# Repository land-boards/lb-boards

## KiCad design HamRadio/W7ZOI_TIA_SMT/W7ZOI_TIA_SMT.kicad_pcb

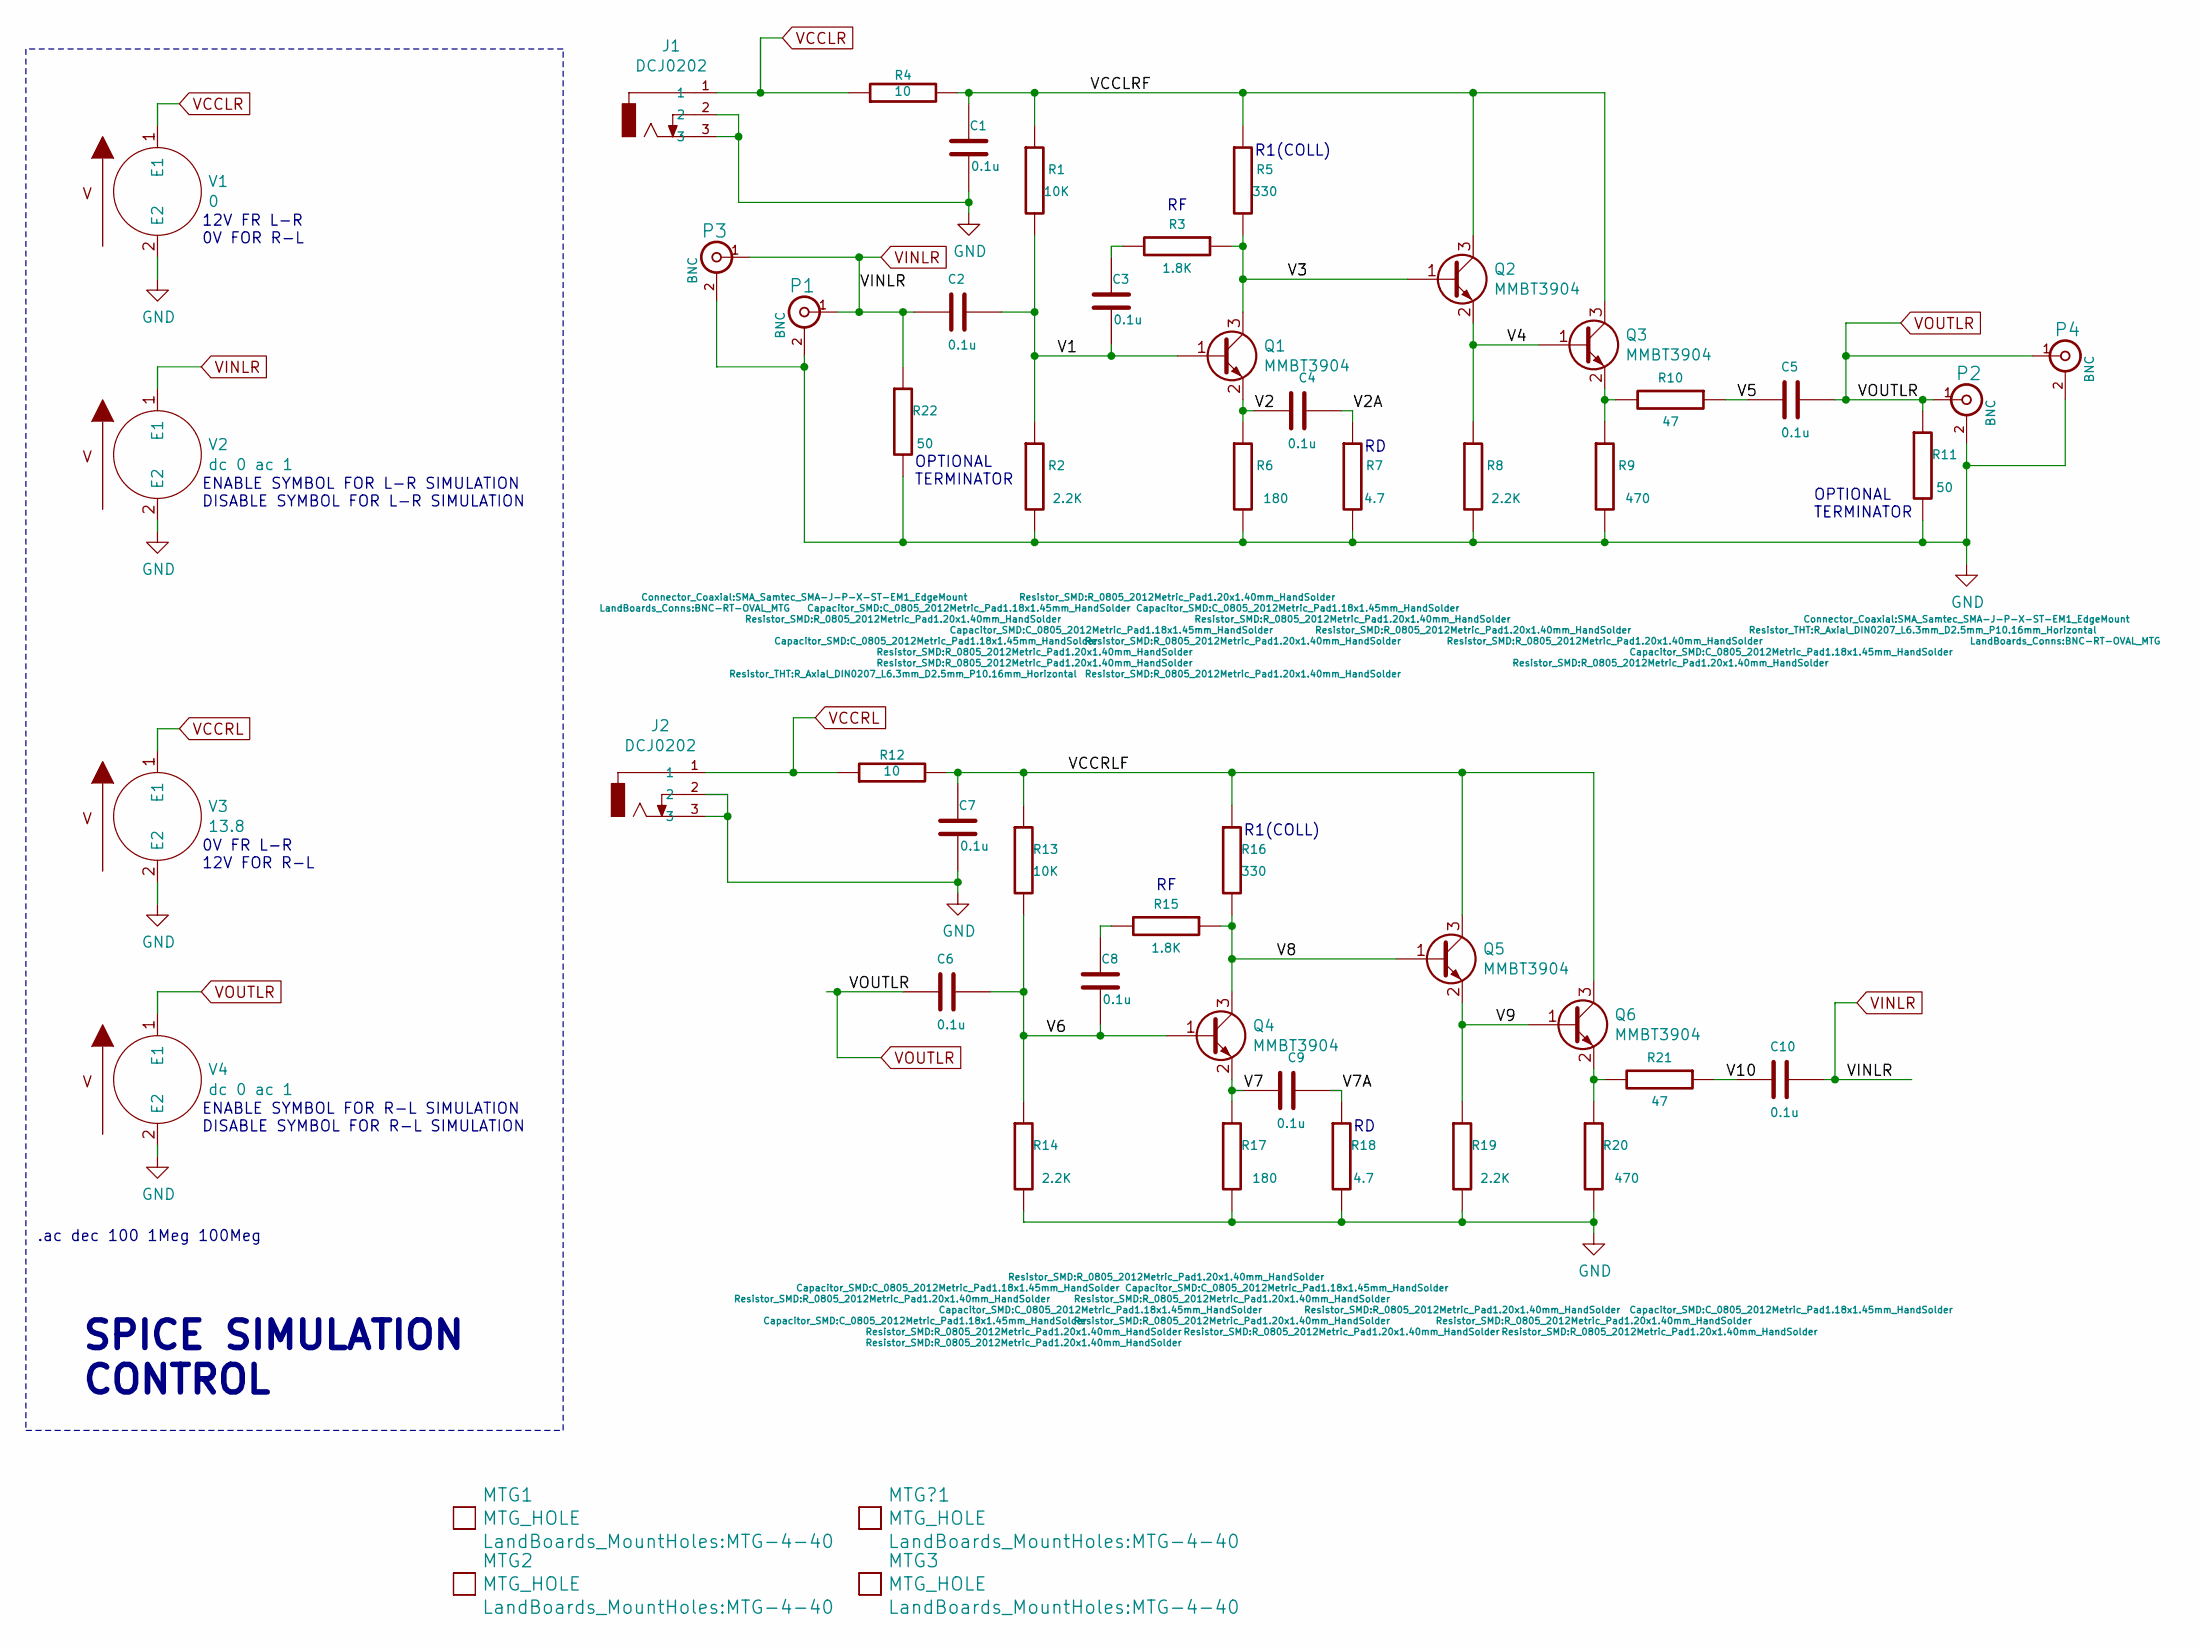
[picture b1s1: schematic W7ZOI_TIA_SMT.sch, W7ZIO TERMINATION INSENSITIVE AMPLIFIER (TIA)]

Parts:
C1, C2, C3, C4, C5, C6, C7, C8, C9, C10: 0.1u; C_0805_2012Metric_Pad1.18x1.45mm_HandSolder
J1, J2: DCJ0202; DCJ-NEW-Slotted
MTG1, MTG2, MTG3: MTG_HOLE; MTG-4-40
MTG?1: MTG_HOLE; MTG-4-40
P1, P2: BNC; SMA_Samtec_SMA-J-P-X-ST-EM1_EdgeMount
P3, P4: BNC; BNC-RT-OVAL_MTG
Q1, Q2, Q3, Q4, Q5, Q6: MMBT3904; SOT-23
R1, R13: 10K; R_0805_2012Metric_Pad1.20x1.40mm_HandSolder
R2, R8, R14, R19: 2.2K; R_0805_2012Metric_Pad1.20x1.40mm_HandSolder
R3, R15: 1.8K; R_0805_2012Metric_Pad1.20x1.40mm_HandSolder
R4, R12: 10; R_0805_2012Metric_Pad1.20x1.40mm_HandSolder
R5, R16: 330; R_0805_2012Metric_Pad1.20x1.40mm_HandSolder
R6, R17: 180; R_0805_2012Metric_Pad1.20x1.40mm_HandSolder
R7, R18: 4.7; R_0805_2012Metric_Pad1.20x1.40mm_HandSolder
R9, R20: 470; R_0805_2012Metric_Pad1.20x1.40mm_HandSolder
R10, R21: 47; R_0805_2012Metric_Pad1.20x1.40mm_HandSolder
R11, R22: 50; R_Axial_DIN0207_L6.3mm_D2.5mm_P10.16mm_Horizontal
V1: 0
V2, V4: dc 0 ac 1
V3: 13.8

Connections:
/V1: C2.1, C3.2, Q1.1 (B), R1.2, R2.1
/V2: C4.2, Q1.2 (E), R6.1
/V2A: C4.1, R7.1
/V3: Q1.3 (C), Q2.1 (B), R3.1, R5.2
/V4: Q2.2 (E), Q3.1 (B), R8.1
/V5: C5.2, R10.1
/V6: C6.1, C8.2, Q4.1 (B), R13.2, R14.1
/V7: C9.2, Q4.2 (E), R17.1
/V7A: C9.1, R18.1
/V8: Q4.3 (C), Q5.1 (B), R15.1, R16.2
/V9: Q5.2 (E), Q6.1 (B), R19.1
/V10: C10.2, R21.1
/VCCLRF: C1.1, Q2.3 (C), Q3.3 (C), R1.1, R4.2, R5.1
/VCCRLF: C7.1, Q5.3 (C), Q6.3 (C), R12.2, R13.1, R16.1
GND: C1.2, C7.2, J1.2, J1.3, J2.2, J2.3, P1.2 (Ext), P2.2 (Ext), P3.2 (Ext), P4.2 (Ext), R2.2, R6.2, R7.2, R8.2, R9.2, R11.2, R14.2, R17.2, R18.2, R19.2, R20.2, R22.2, V1.2 (E2), V2.2 (E2), V3.2 (E2), V4.2 (E2)
unnamed: C3.1, R3.2
unnamed: C8.1, R15.2
unnamed: Q3.2 (E), R9.1, R10.2
unnamed: Q6.2 (E), R20.1, R21.2
VCCLR: J1.1, R4.1, V1.1 (E1)
VCCRL: J2.1, R12.1, V3.1 (E1)
VINLR: C2.2, C10.1, P1.1 (In), P3.1 (In), R22.1, V2.1 (E1)
VOUTLR: C5.1, C6.2, P2.1 (In), P4.1 (In), R11.1, V4.1 (E1)

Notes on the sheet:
.ac dec 100 1Meg 100Meg
R1(COLL)
12V FR L-R 0V FOR R-L
0V FR L-R 12V FOR R-L
ENABLE SYMBOL FOR L-R SIMULATION DISABLE SYMBOL FOR L-R SIMULATION
ENABLE SYMBOL FOR R-L SIMULATION DISABLE SYMBOL FOR R-L SIMULATION
SPICE SIMULATION CONTROL
OPTIONAL TERMINATOR

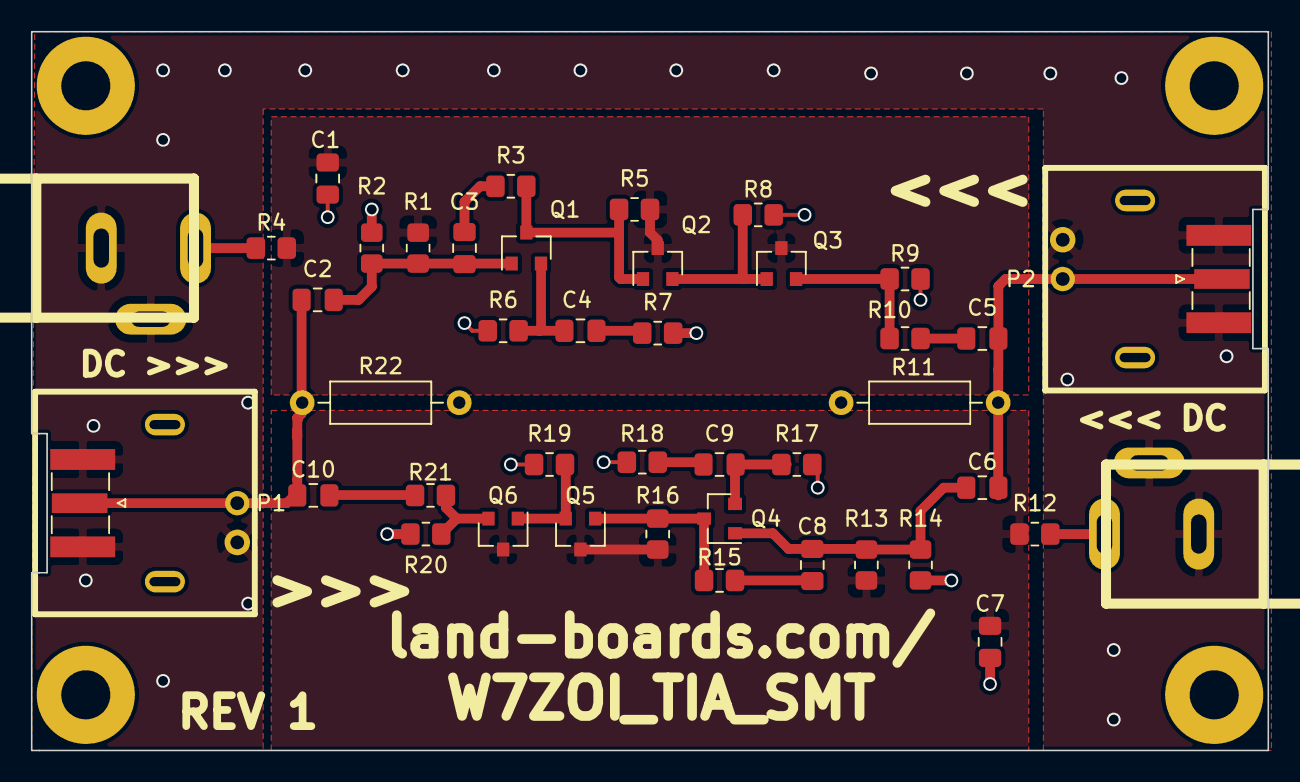
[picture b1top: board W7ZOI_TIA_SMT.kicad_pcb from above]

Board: 2 copper layers, 80.0 x 46.5 mm, 48 parts (0 on the bottom side), 23 nets.

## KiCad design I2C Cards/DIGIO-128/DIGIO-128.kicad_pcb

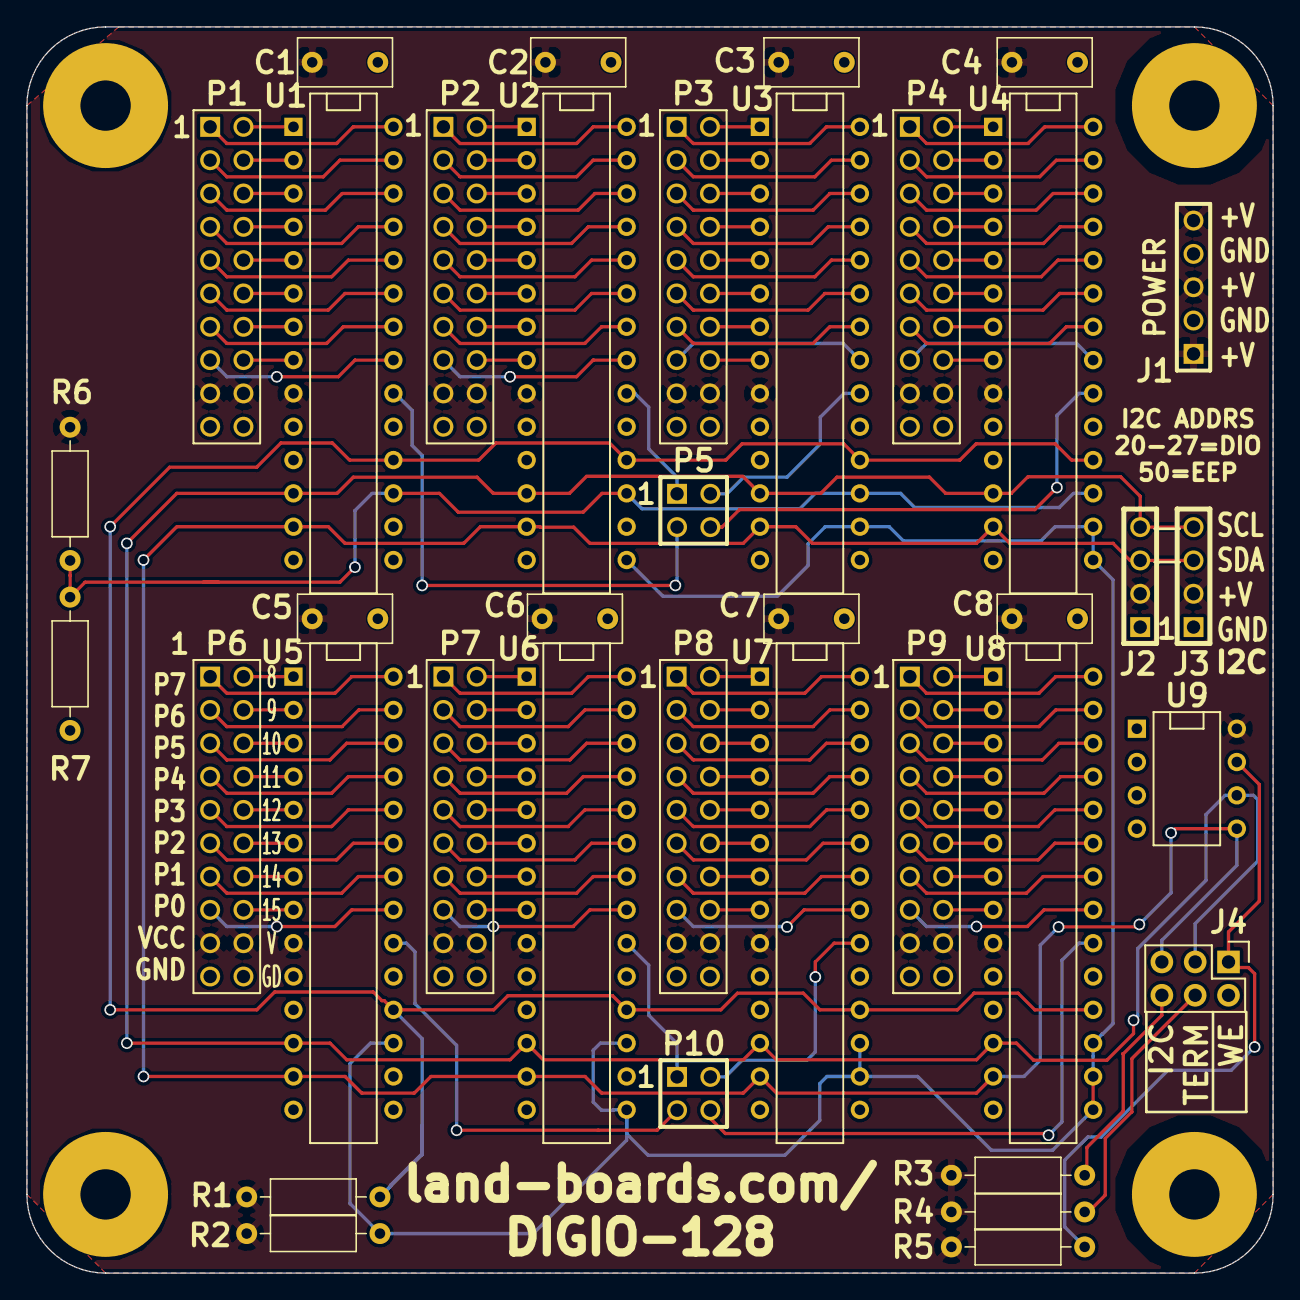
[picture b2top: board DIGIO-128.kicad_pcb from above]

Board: 2 copper layers, 95.0 x 95.0 mm, 42 parts (0 on the bottom side), 146 nets.

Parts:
C1, C2, C3, C4, C5, C6, C7, C8: C; C_Rect_L7.0mm_W3.5mm_P5.00mm
J1: CONN_5; PIN_ARRAY_5X1
J2, J3: CONN_4; pin_array_4x1
J4: CONN_02X03; Pin_Header_Straight_2x03
MTG1, MTG2, MTG3, MTG4: MTG_HOLE; MTG-6-32
P1, P2, P3, P4, P6, P7, P8, P9: CONN_20; PIN_ARRAY_10X2
P5, P10: CONN_2X2; PIN_ARRAY_2X2
R1, R2, R6: 10K; R_Axial_DIN0207_L6.3mm_D2.5mm_P10.16mm_Horizontal
R3, R4: 2.2K; R_Axial_DIN0207_L6.3mm_D2.5mm_P10.16mm_Horizontal
R5: 1K; R_Axial_DIN0207_L6.3mm_D2.5mm_P10.16mm_Horizontal
R7: 0; R_Axial_DIN0207_L6.3mm_D2.5mm_P10.16mm_Horizontal
U1, U2, U3, U4, U5, U6, U7, U8: MCP23017P; DIP-28__300
U9: 24LC024-I/P; DIP-8__300

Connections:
/16-bits-1/A2: R6.2, R7.1, U1.17 (A2), U2.17 (A2), U3.17 (A2), U4.17 (A2)
/16-bits-1/GP0: P1.15, U1.21 (GPA0)
/16-bits-1/GP1: P1.13, U1.22 (GPA1)
/16-bits-1/GP2: P1.11, U1.23 (GPA2)
/16-bits-1/GP3: P1.9, U1.24 (GPS3)
/16-bits-1/GP4: P1.7, U1.25 (GPA4)
/16-bits-1/GP5: P1.5, U1.26 (GPA5)
/16-bits-1/GP6: P1.3, U1.27 (GPA6)
/16-bits-1/GP7: P1.1, U1.28 (GPA7)
/16-bits-1/GP8: P1.2, U1.1 (GPB0)
/16-bits-1/GP9: P1.4, U1.2 (GPB1)
/16-bits-1/GP10: P1.6, U1.3 (GPB2)
/16-bits-1/GP11: P1.8, U1.4 (GPB3)
/16-bits-1/GP12: P1.10, U1.5 (GPB4)
/16-bits-1/GP13: P1.12, U1.6 (GPB5)
/16-bits-1/GP14: P1.14, U1.7 (GPB6)
/16-bits-1/GP15: P1.16, U1.8 (GPB7)
/16-bits-2/GP0: P2.15, U2.21 (GPA0)
/16-bits-2/GP1: P2.13, U2.22 (GPA1)
/16-bits-2/GP2: P2.11, U2.23 (GPA2)
/16-bits-2/GP3: P2.9, U2.24 (GPS3)
/16-bits-2/GP4: P2.7, U2.25 (GPA4)
/16-bits-2/GP5: P2.5, U2.26 (GPA5)
/16-bits-2/GP6: P2.3, U2.27 (GPA6)
/16-bits-2/GP7: P2.1, U2.28 (GPA7)
/16-bits-2/GP8: P2.2, U2.1 (GPB0)
/16-bits-2/GP9: P2.4, U2.2 (GPB1)
/16-bits-2/GP10: P2.6, U2.3 (GPB2)
/16-bits-2/GP11: P2.8, U2.4 (GPB3)
/16-bits-2/GP12: P2.10, U2.5 (GPB4)
/16-bits-2/GP13: P2.12, U2.6 (GPB5)
/16-bits-2/GP14: P2.14, U2.7 (GPB6)
/16-bits-2/GP15: P2.16, U2.8 (GPB7)
/16-bits-3/GP0: P3.15, U3.21 (GPA0)
/16-bits-3/GP1: P3.13, U3.22 (GPA1)
/16-bits-3/GP2: P3.11, U3.23 (GPA2)
/16-bits-3/GP3: P3.9, U3.24 (GPS3)
/16-bits-3/GP4: P3.7, U3.25 (GPA4)
/16-bits-3/GP5: P3.5, U3.26 (GPA5)
/16-bits-3/GP6: P3.3, U3.27 (GPA6)
/16-bits-3/GP7: P3.1, U3.28 (GPA7)
/16-bits-3/GP8: P3.2, U3.1 (GPB0)
/16-bits-3/GP9: P3.4, U3.2 (GPB1)
/16-bits-3/GP10: P3.6, U3.3 (GPB2)
/16-bits-3/GP11: P3.8, U3.4 (GPB3)
/16-bits-3/GP12: P3.10, U3.5 (GPB4)
/16-bits-3/GP13: P3.12, U3.6 (GPB5)
/16-bits-3/GP14: P3.14, U3.7 (GPB6)
/16-bits-3/GP15: P3.16, U3.8 (GPB7)
/16-bits-4/GP0: P4.15, U4.21 (GPA0)
/16-bits-4/GP1: P4.13, U4.22 (GPA1)
/16-bits-4/GP2: P4.11, U4.23 (GPA2)
/16-bits-4/GP3: P4.9, U4.24 (GPS3)
/16-bits-4/GP4: P4.7, U4.25 (GPA4)
/16-bits-4/GP5: P4.5, U4.26 (GPA5)
/16-bits-4/GP6: P4.3, U4.27 (GPA6)
/16-bits-4/GP7: P4.1, U4.28 (GPA7)
/16-bits-4/GP8: P4.2, U4.1 (GPB0)
/16-bits-4/GP9: P4.4, U4.2 (GPB1)
/16-bits-4/GP10: P4.6, U4.3 (GPB2)
/16-bits-4/GP11: P4.8, U4.4 (GPB3)
/16-bits-4/GP12: P4.10, U4.5 (GPB4)
/16-bits-4/GP13: P4.12, U4.6 (GPB5)
/16-bits-4/GP14: P4.14, U4.7 (GPB6)
/16-bits-4/GP15: P4.16, U4.8 (GPB7)
/16-bits-5/GP0: P6.15, U5.21 (GPA0)
/16-bits-5/GP1: P6.13, U5.22 (GPA1)
/16-bits-5/GP2: P6.11, U5.23 (GPA2)
/16-bits-5/GP3: P6.9, U5.24 (GPS3)
/16-bits-5/GP4: P6.7, U5.25 (GPA4)
/16-bits-5/GP5: P6.5, U5.26 (GPA5)
/16-bits-5/GP6: P6.3, U5.27 (GPA6)
/16-bits-5/GP7: P6.1, U5.28 (GPA7)
/16-bits-5/GP8: P6.2, U5.1 (GPB0)
/16-bits-5/GP9: P6.4, U5.2 (GPB1)
/16-bits-5/GP10: P6.6, U5.3 (GPB2)
/16-bits-5/GP11: P6.8, U5.4 (GPB3)
/16-bits-5/GP12: P6.10, U5.5 (GPB4)
/16-bits-5/GP13: P6.12, U5.6 (GPB5)
/16-bits-5/GP14: P6.14, U5.7 (GPB6)
/16-bits-5/GP15: P6.16, U5.8 (GPB7)
/16-bits-6/GP0: P7.15, U6.21 (GPA0)
/16-bits-6/GP1: P7.13, U6.22 (GPA1)
/16-bits-6/GP2: P7.11, U6.23 (GPA2)
/16-bits-6/GP3: P7.9, U6.24 (GPS3)
/16-bits-6/GP4: P7.7, U6.25 (GPA4)
/16-bits-6/GP5: P7.5, U6.26 (GPA5)
/16-bits-6/GP6: P7.3, U6.27 (GPA6)
/16-bits-6/GP7: P7.1, U6.28 (GPA7)
/16-bits-6/GP8: P7.2, U6.1 (GPB0)
/16-bits-6/GP9: P7.4, U6.2 (GPB1)
/16-bits-6/GP10: P7.6, U6.3 (GPB2)
/16-bits-6/GP11: P7.8, U6.4 (GPB3)
/16-bits-6/GP12: P7.10, U6.5 (GPB4)
/16-bits-6/GP13: P7.12, U6.6 (GPB5)
/16-bits-6/GP14: P7.14, U6.7 (GPB6)
/16-bits-6/GP15: P7.16, U6.8 (GPB7)
/16-bits-7/GP0: P8.15, U7.21 (GPA0)
/16-bits-7/GP1: P8.13, U7.22 (GPA1)
/16-bits-7/GP2: P8.11, U7.23 (GPA2)
/16-bits-7/GP3: P8.9, U7.24 (GPS3)
/16-bits-7/GP4: P8.7, U7.25 (GPA4)
/16-bits-7/GP5: P8.5, U7.26 (GPA5)
/16-bits-7/GP6: P8.3, U7.27 (GPA6)
/16-bits-7/GP7: P8.1, U7.28 (GPA7)
/16-bits-7/GP8: P8.2, U7.1 (GPB0)
/16-bits-7/GP9: P8.4, U7.2 (GPB1)
/16-bits-7/GP10: P8.6, U7.3 (GPB2)
/16-bits-7/GP11: P8.8, U7.4 (GPB3)
/16-bits-7/GP12: P8.10, U7.5 (GPB4)
/16-bits-7/GP13: P8.12, U7.6 (GPB5)
/16-bits-7/GP14: P8.14, U7.7 (GPB6)
/16-bits-7/GP15: P8.16, U7.8 (GPB7)
/16-bits-8/GP0: P9.15, U8.21 (GPA0)
/16-bits-8/GP1: P9.13, U8.22 (GPA1)
/16-bits-8/GP2: P9.11, U8.23 (GPA2)
/16-bits-8/GP3: P9.9, U8.24 (GPS3)
/16-bits-8/GP4: P9.7, U8.25 (GPA4)
/16-bits-8/GP5: P9.5, U8.26 (GPA5)
/16-bits-8/GP6: P9.3, U8.27 (GPA6)
/16-bits-8/GP7: P9.1, U8.28 (GPA7)
/16-bits-8/GP8: P9.2, U8.1 (GPB0)
/16-bits-8/GP9: P9.4, U8.2 (GPB1)
/16-bits-8/GP10: P9.6, U8.3 (GPB2)
/16-bits-8/GP11: P9.8, U8.4 (GPB3)
/16-bits-8/GP12: P9.10, U8.5 (GPB4)
/16-bits-8/GP13: P9.12, U8.6 (GPB5)
/16-bits-8/GP14: P9.14, U8.7 (GPB6)
/16-bits-8/GP15: P9.16, U8.8 (GPB7)
/AEQ1: R2.2, U2.15 (A0), U3.16 (A1), U4.15 (A0), U4.16 (A1), U5.17 (A2), U6.15 (A0), U6.17 (A2), U7.16 (A1), U7.17 (A2), U8.15 (A0), U8.16 (A1), U8.17 (A2)
/INT0: P5.3, U1.20 (INTA)
/INT1: P5.1, U2.20 (INTA)
/INT2: P5.2, U3.20 (INTA)
/INT3: P5.4, U4.20 (INTA)
/INT4: P10.3, U5.20 (INTA)
/INT5: P10.1, U6.20 (INTA)
/INT6: P10.2, U7.20 (INTA)
/INT7: P10.4, U8.20 (INTA)
/RST1: R1.2, U1.18 (~RST), U2.18 (~RST), U3.18 (~RST), U4.18 (~RST), U5.18 (~RST), U6.18 (~RST), U7.18 (~RST), U8.18 (~RST)
/SCL: J2.4, J3.4, J4.3, U1.12 (SCL), U2.12 (SCL), U3.12 (SCL), U4.12 (SCL), U5.12 (SCL), U6.12 (SCL), U7.12 (SCL), U8.12 (SCL), U9.6 (SCL)
/SDA: J2.3, J3.3, J4.5, U1.13 (SDA), U2.13 (SDA), U3.13 (SDA), U4.13 (SDA), U5.13 (SDA), U6.13 (SDA), U7.13 (SDA), U8.13 (SDA), U9.5 (SDA)
/VCC: C1.1, C2.1, C3.1, C4.1, C5.1, C6.1, C7.1, C8.1, J1.1, J1.3, J1.5, J2.2, J3.2, P1.17, P1.18, P2.17, P2.18, P3.17, P3.18, P4.17, P4.18, P6.17, P6.18, P7.17, P7.18, P8.17, P8.18, P9.17, P9.18, R1.1, R2.1, R3.2, R4.2, R5.1, R6.1, U1.9 (VDD), U2.9 (VDD), U3.9 (VDD), U4.9 (VDD), U5.9 (VDD), U6.9 (VDD), U7.9 (VDD), U8.9 (VDD), U9.8 (VCC)
/WE: J4.1, R5.2, U9.7 (TEST)
GND: C1.2, C2.2, C3.2, C4.2, C5.2, C6.2, C7.2, C8.2, J1.2, J1.4, J2.1, J3.1, J4.2, P1.19, P1.20, P2.19, P2.20, P3.19, P3.20, P4.19, P4.20, P6.19, P6.20, P7.19, P7.20, P8.19, P8.20, P9.19, P9.20, R7.2, U1.10 (VSS), U1.15 (A0), U1.16 (A1), U2.10 (VSS), U2.16 (A1), U3.10 (VSS), U3.15 (A0), U4.10 (VSS), U5.10 (VSS), U5.15 (A0), U5.16 (A1), U6.10 (VSS), U6.16 (A1), U7.10 (VSS), U7.15 (A0), U8.10 (VSS), U9.1 (A0), U9.2 (A1), U9.3 (A2), U9.4 (GND)
unnamed: J4.4, R4.1
unnamed: J4.6, R3.1

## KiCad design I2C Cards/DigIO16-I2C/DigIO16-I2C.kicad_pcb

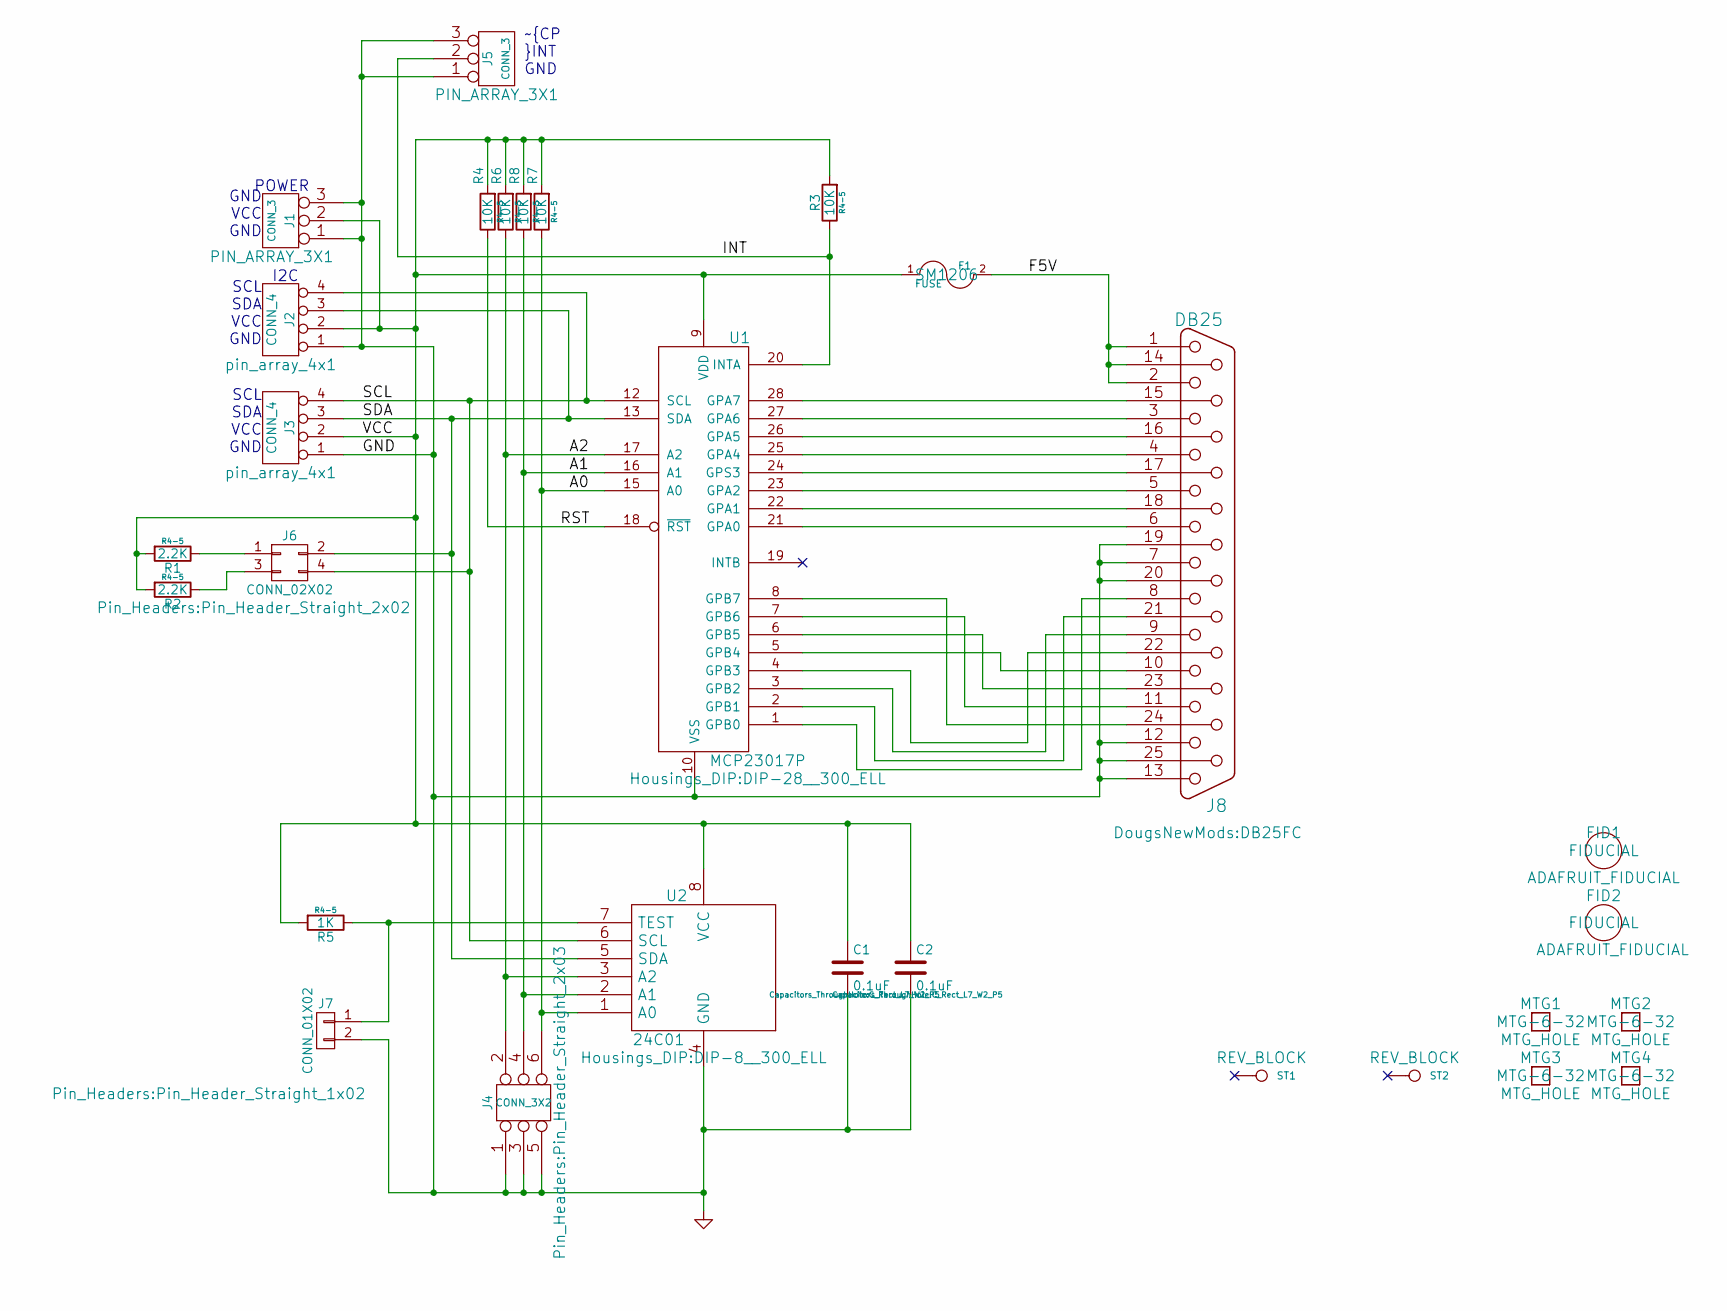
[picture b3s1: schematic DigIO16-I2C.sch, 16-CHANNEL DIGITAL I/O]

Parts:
C1, C2: 0.1uF; C_Rect_L7_W2_P5
F1: FUSE; SM1206
FID1, FID2: ADAFRUIT_FIDUCIAL; FIDUCIAL
J1, J5: CONN_3; PIN_ARRAY_3X1
J2, J3: CONN_4; pin_array_4x1
J4: CONN_3X2; Pin_Header_Straight_2x03
J6: CONN_02X02; Pin_Header_Straight_2x02
J7: CONN_01X02; Pin_Header_Straight_1x02
J8: DB25; DB25FC
MTG1, MTG2, MTG3, MTG4: MTG_HOLE; MTG-6-32
R1, R2: 2.2K; R4-5
R3, R4, R6, R7, R8: 10K; R4-5
R5: 1K; R4-5
ST1, ST2: CONN_1; REV_BLOCK
U1: MCP23017P; DIP-28__300_ELL
U2: 24C01; DIP-8__300_ELL

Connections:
/A0: J4.6, R7.1, U1.15 (A0), U2.1 (A0)
/A1: J4.4, R8.1, U1.16 (A1), U2.2 (A1)
/A2: J4.2, R6.1, U1.17 (A2), U2.3 (A2)
/F5V: F1.2, J8.1, J8.2, J8.14
/INT: J5.2 (PM), R3.1, U1.20 (INTA)
/RST: R4.1, U1.18 (~RST)
/SCL: J2.4, J3.4, J6.4, U1.12 (SCL), U2.6 (SCL)
/SDA: J2.3, J3.3, J6.2, U1.13 (SDA), U2.5 (SDA)
/VCC: C1.1, C2.1, F1.1, J1.2 (PM), J2.2, J3.2, R1.2, R2.2, R3.2, R4.2, R5.2, R6.2, R7.2, R8.2, U1.9 (VDD), U2.8 (VCC)
GND: C1.2, C2.2, J1.1, J1.3, J2.1, J3.1, J4.1, J4.3, J4.5, J5.1, J5.3, J7.2, J8.7, J8.12, J8.13, J8.19, J8.20, J8.25, U1.10 (VSS), U2.4 (GND)
unnamed: J6.1, R1.1
unnamed: J6.3, R2.1
unnamed: J7.1, R5.1, U2.7 (TEST)
unnamed: J8.3, U1.27 (GPA6)
unnamed: J8.4, U1.25 (GPA4)
unnamed: J8.5, U1.23 (GPA2)
unnamed: J8.6, U1.21 (GPA0)
unnamed: J8.8, U1.1 (GPB0)
unnamed: J8.9, U1.3 (GPB2)
unnamed: J8.10, U1.5 (GPB4)
unnamed: J8.11, U1.7 (GPB6)
unnamed: J8.15, U1.28 (GPA7)
unnamed: J8.16, U1.26 (GPA5)
unnamed: J8.17, U1.24 (GPS3)
unnamed: J8.18, U1.22 (GPA1)
unnamed: J8.21, U1.2 (GPB1)
unnamed: J8.22, U1.4 (GPB3)
unnamed: J8.23, U1.6 (GPB5)
unnamed: J8.24, U1.8 (GPB7)

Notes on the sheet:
SCL SDA VCC GND
GND VCC GND
~CP ~INT GND
POWER
I2C

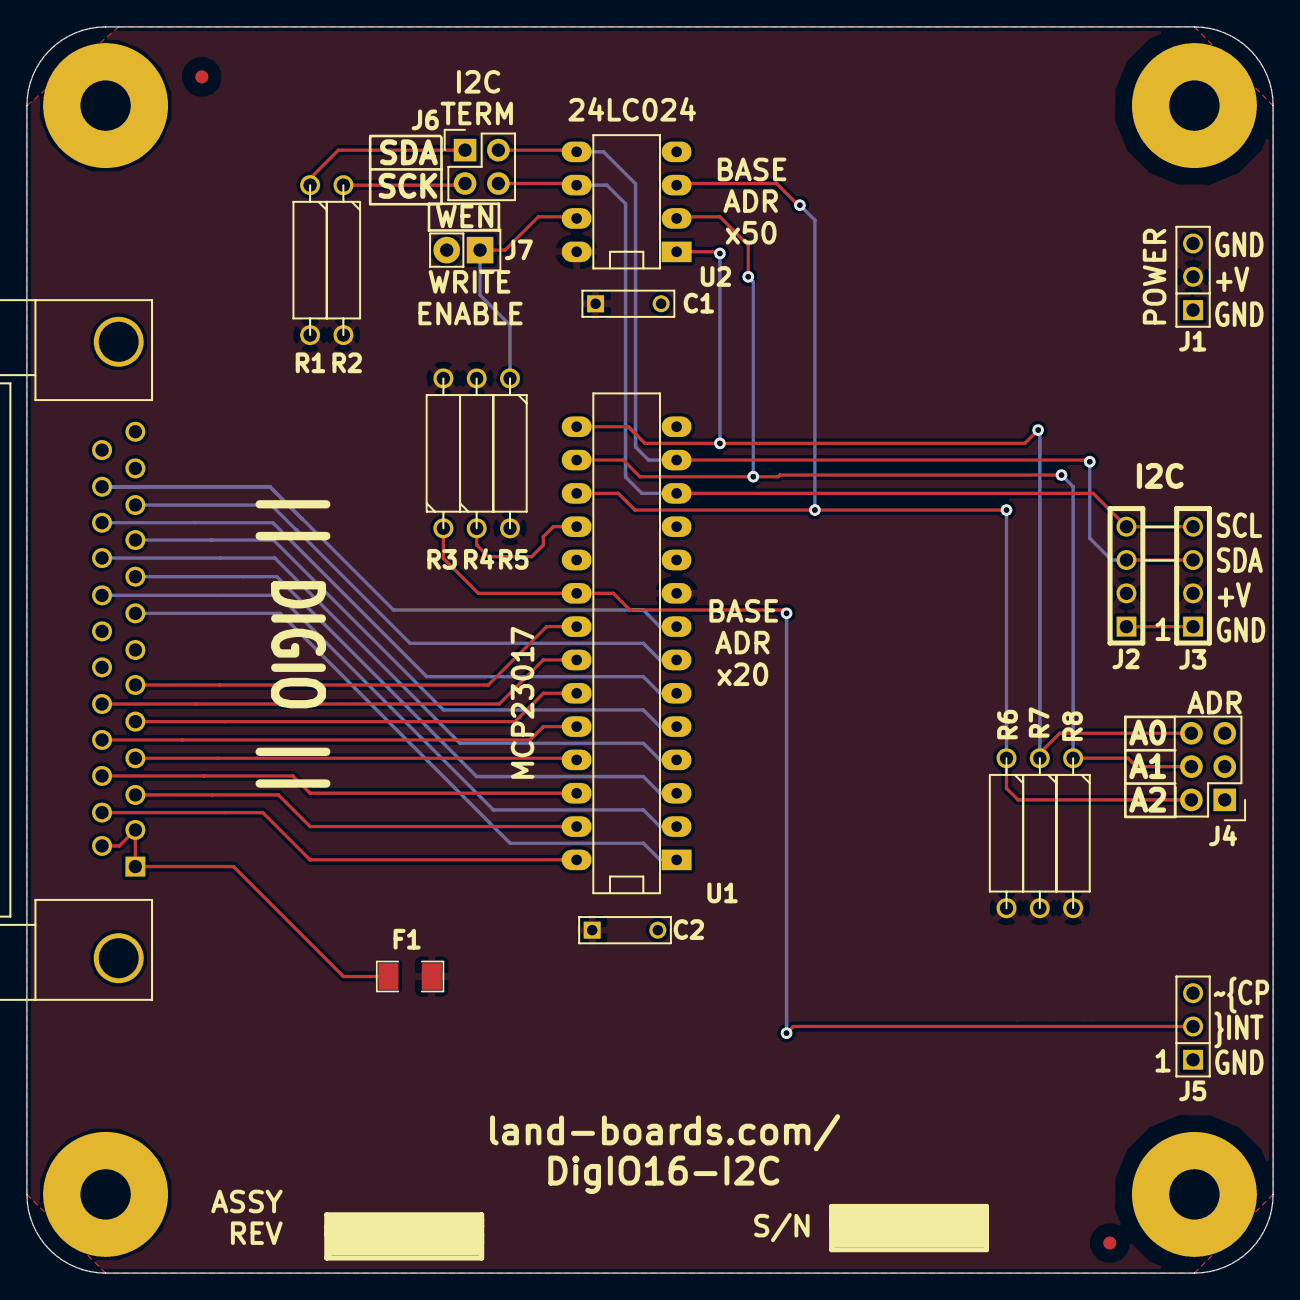
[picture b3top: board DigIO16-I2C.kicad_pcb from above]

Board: 2 copper layers, 95.0 x 95.0 mm, 30 parts (0 on the bottom side), 29 nets.

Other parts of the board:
TESTED: VAL**; TEST_BLK-REAR

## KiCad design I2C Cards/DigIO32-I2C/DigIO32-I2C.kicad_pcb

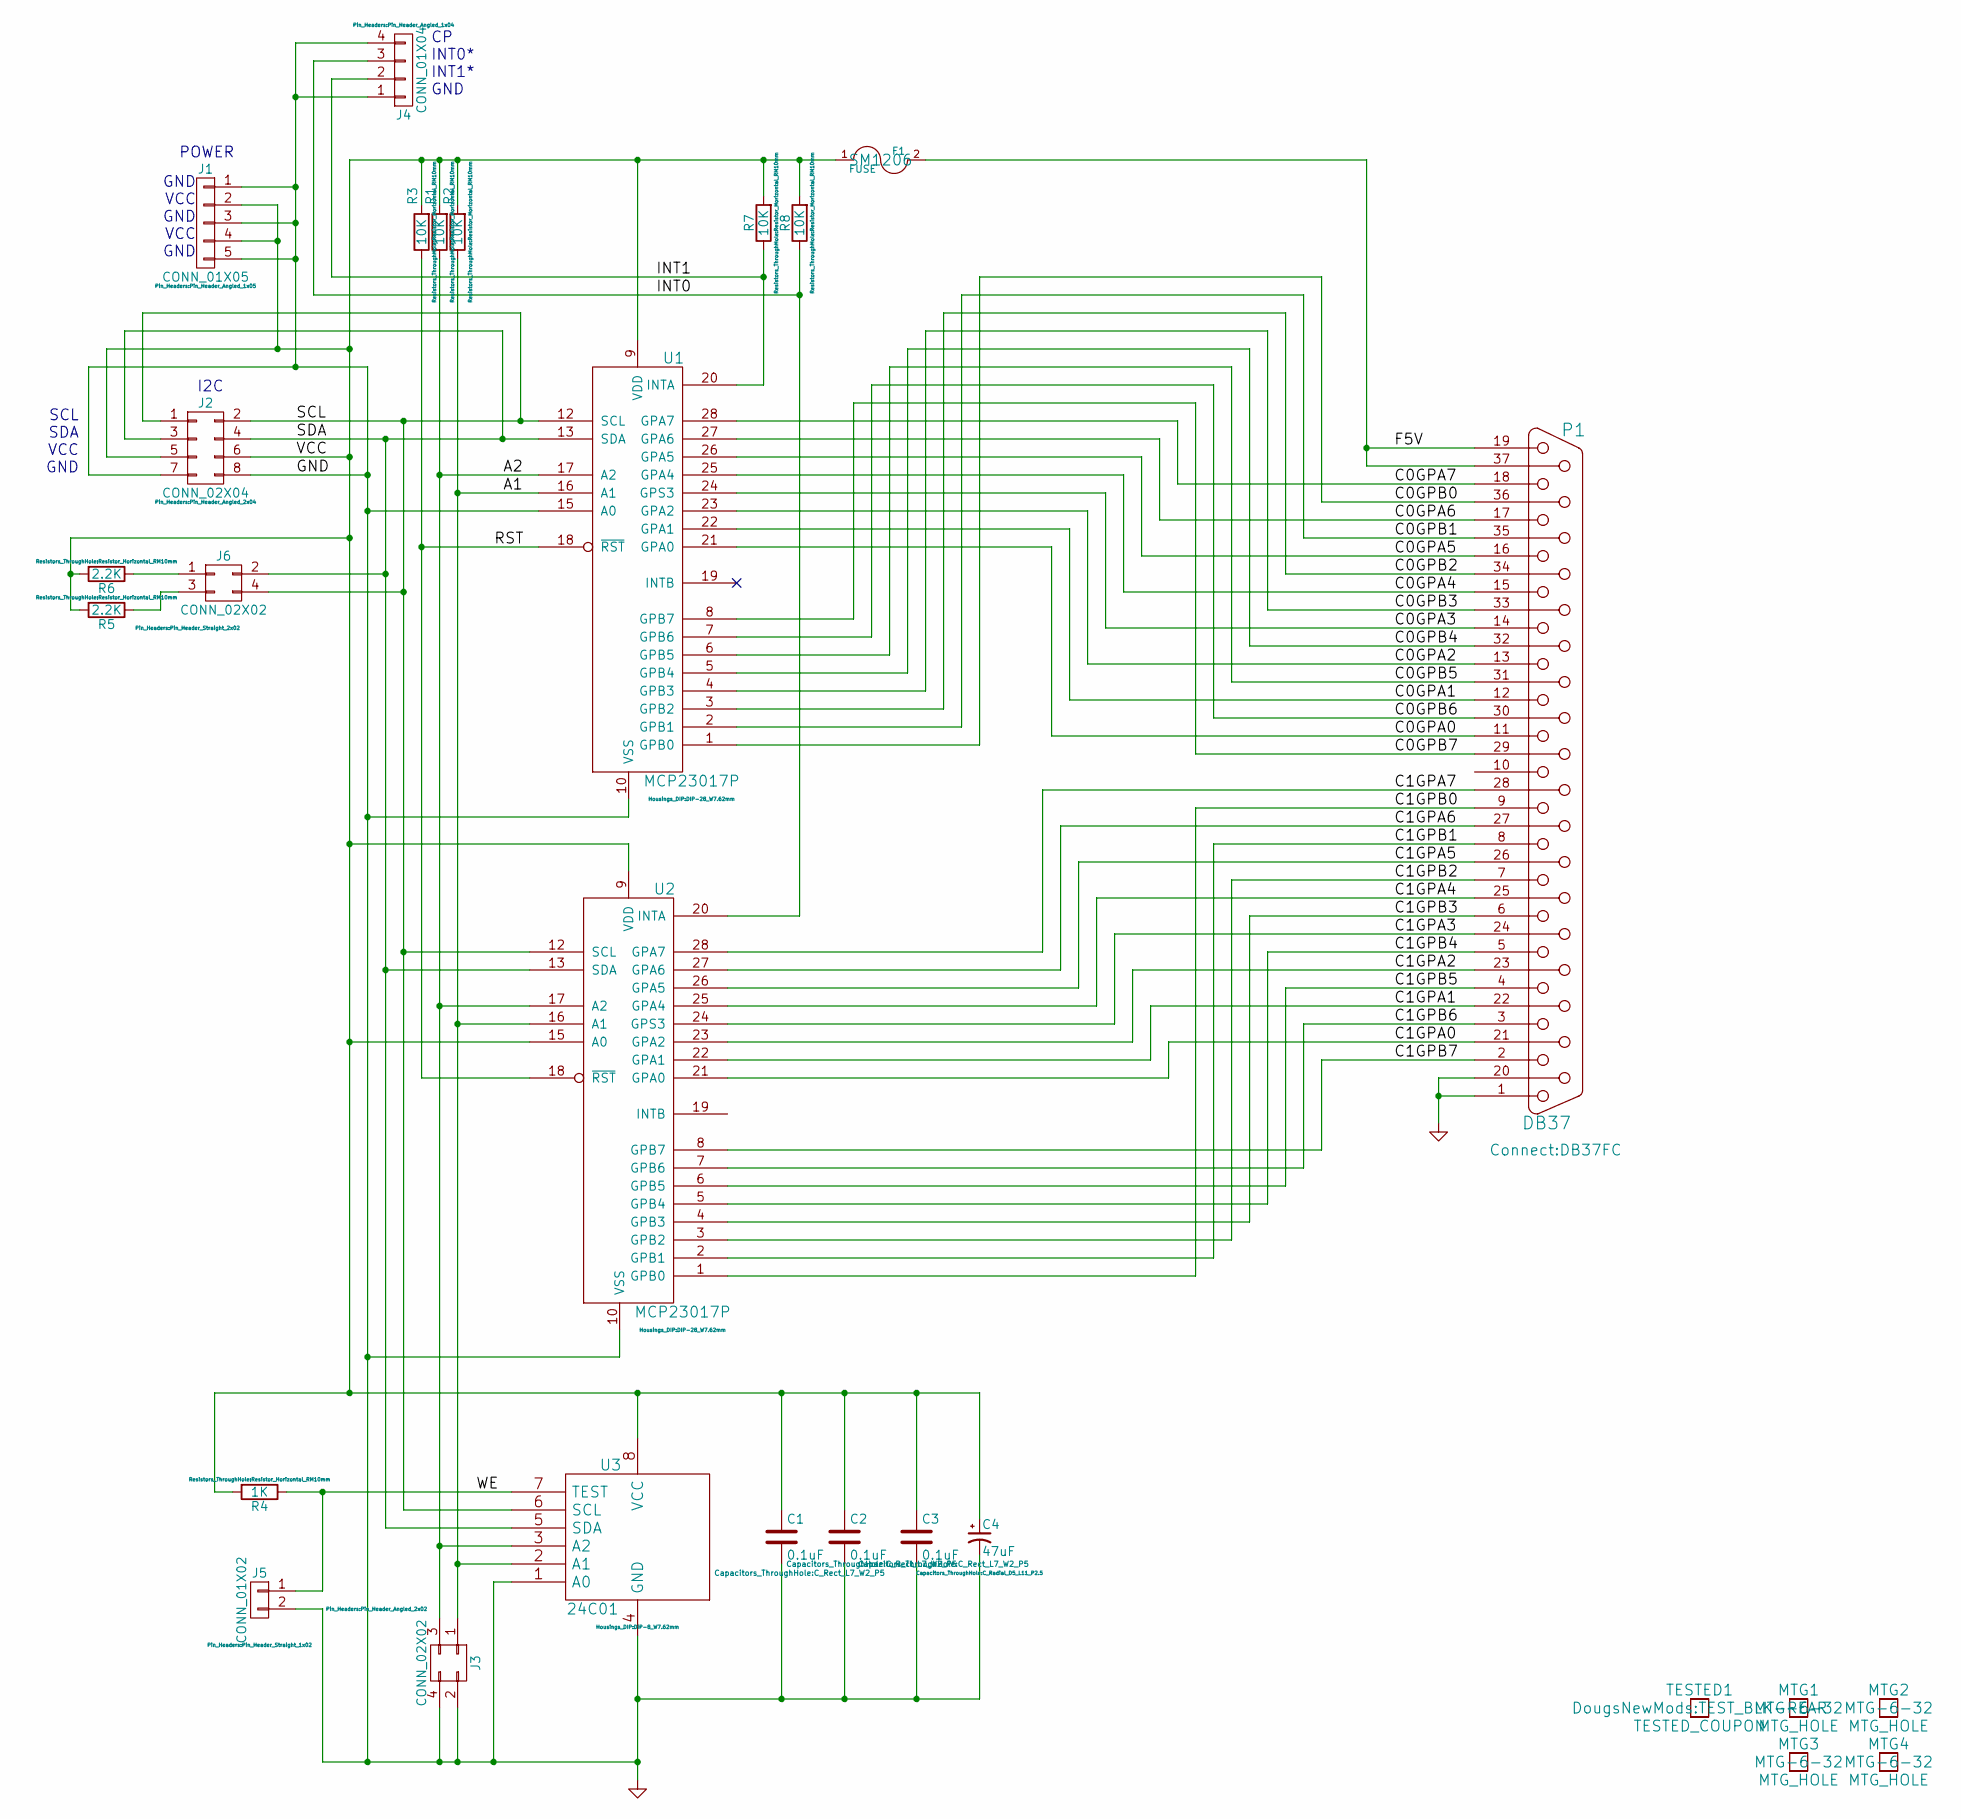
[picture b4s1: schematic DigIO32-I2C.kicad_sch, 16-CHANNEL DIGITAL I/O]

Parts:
C1, C2, C3: 0.1uF; C_Rect_L7_W2_P5
C4: 47uF; C_Radial_D5_L11_P2.5
F1: FUSE; SM1206
J1: CONN_01X05; Pin_Header_Angled_1x05
J2: CONN_02X04; Pin_Header_Angled_2x04
J3: CONN_02X02; Pin_Header_Angled_2x02
J4: CONN_01X04; Pin_Header_Angled_1x04
J5: CONN_01X02; Pin_Header_Straight_1x02
J6: CONN_02X02; Pin_Header_Straight_2x02
MTG1, MTG2, MTG3, MTG4: MTG_HOLE; MTG-6-32
P1: DB37; DB37FC
R1, R2, R3, R7, R8: 10K; Resistor_Horizontal_RM10mm
R4: 1K; Resistor_Horizontal_RM10mm
R5, R6: 2.2K; Resistor_Horizontal_RM10mm
TESTED1: TESTED_COUPON; TEST_BLK-REAR
U1, U2: MCP23017P; DIP-28_W7.62mm
U3: 24C01; DIP-8_W7.62mm

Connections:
/A1: J3.1, R2.1, U1.16 (A1), U2.16 (A1), U3.2 (A1)
/A2: J3.3, R1.1, U1.17 (A2), U2.17 (A2), U3.3 (A2)
/C0GPA0: P1.11, U1.21 (GPA0)
/C0GPA1: P1.12, U1.22 (GPA1)
/C0GPA2: P1.13, U1.23 (GPA2)
/C0GPA3: P1.14, U1.24 (GPS3)
/C0GPA4: P1.15, U1.25 (GPA4)
/C0GPA5: P1.16, U1.26 (GPA5)
/C0GPA6: P1.17, U1.27 (GPA6)
/C0GPA7: P1.18, U1.28 (GPA7)
/C0GPB0: P1.36, U1.1 (GPB0)
/C0GPB1: P1.35, U1.2 (GPB1)
/C0GPB2: P1.34, U1.3 (GPB2)
/C0GPB3: P1.33, U1.4 (GPB3)
/C0GPB4: P1.32, U1.5 (GPB4)
/C0GPB5: P1.31, U1.6 (GPB5)
/C0GPB6: P1.30, U1.7 (GPB6)
/C0GPB7: P1.29, U1.8 (GPB7)
/C1GPA0: P1.21, U2.21 (GPA0)
/C1GPA1: P1.22, U2.22 (GPA1)
/C1GPA2: P1.23, U2.23 (GPA2)
/C1GPA3: P1.24, U2.24 (GPS3)
/C1GPA4: P1.25, U2.25 (GPA4)
/C1GPA5: P1.26, U2.26 (GPA5)
/C1GPA6: P1.27, U2.27 (GPA6)
/C1GPA7: P1.28, U2.28 (GPA7)
/C1GPB0: P1.9, U2.1 (GPB0)
/C1GPB1: P1.8, U2.2 (GPB1)
/C1GPB2: P1.7, U2.3 (GPB2)
/C1GPB3: P1.6, U2.4 (GPB3)
/C1GPB4: P1.5, U2.5 (GPB4)
/C1GPB5: P1.4, U2.6 (GPB5)
/C1GPB6: P1.3, U2.7 (GPB6)
/C1GPB7: P1.2, U2.8 (GPB7)
/F5V: F1.2, P1.19, P1.37
/INT0: J4.3, R8.1, U2.20 (INTA)
/INT1: J4.2, R7.1, U1.20 (INTA)
/RST: R3.1, U1.18 (~RST), U2.18 (~RST)
/SCL: J2.1, J2.2, J6.4, U1.12 (SCL), U2.12 (SCL), U3.6 (SCL)
/SDA: J2.3, J2.4, J6.2, U1.13 (SDA), U2.13 (SDA), U3.5 (SDA)
/VCC: C1.1, C2.1, C3.1, C4.1, F1.1, J1.2, J1.4, J2.5, J2.6, R1.2, R2.2, R3.2, R4.2, R5.2, R6.2, R7.2, R8.2, U1.9 (VDD), U2.9 (VDD), U2.15 (A0), U3.8 (VCC)
/WE: J5.1, R4.1, U3.7 (TEST)
GND: C1.2, C2.2, C3.2, C4.2, J1.1, J1.3, J1.5, J2.7, J2.8, J3.2, J3.4, J4.1, J4.4, J5.2, P1.1, P1.20, U1.10 (VSS), U1.15 (A0), U2.10 (VSS), U3.1 (A0), U3.4 (GND)
unnamed: J6.1, R6.1
unnamed: J6.3, R5.1

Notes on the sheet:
GND VCC GND VCC GND
POWER
SCL SDA VCC GND
I2C
CP INT0* INT1* GND

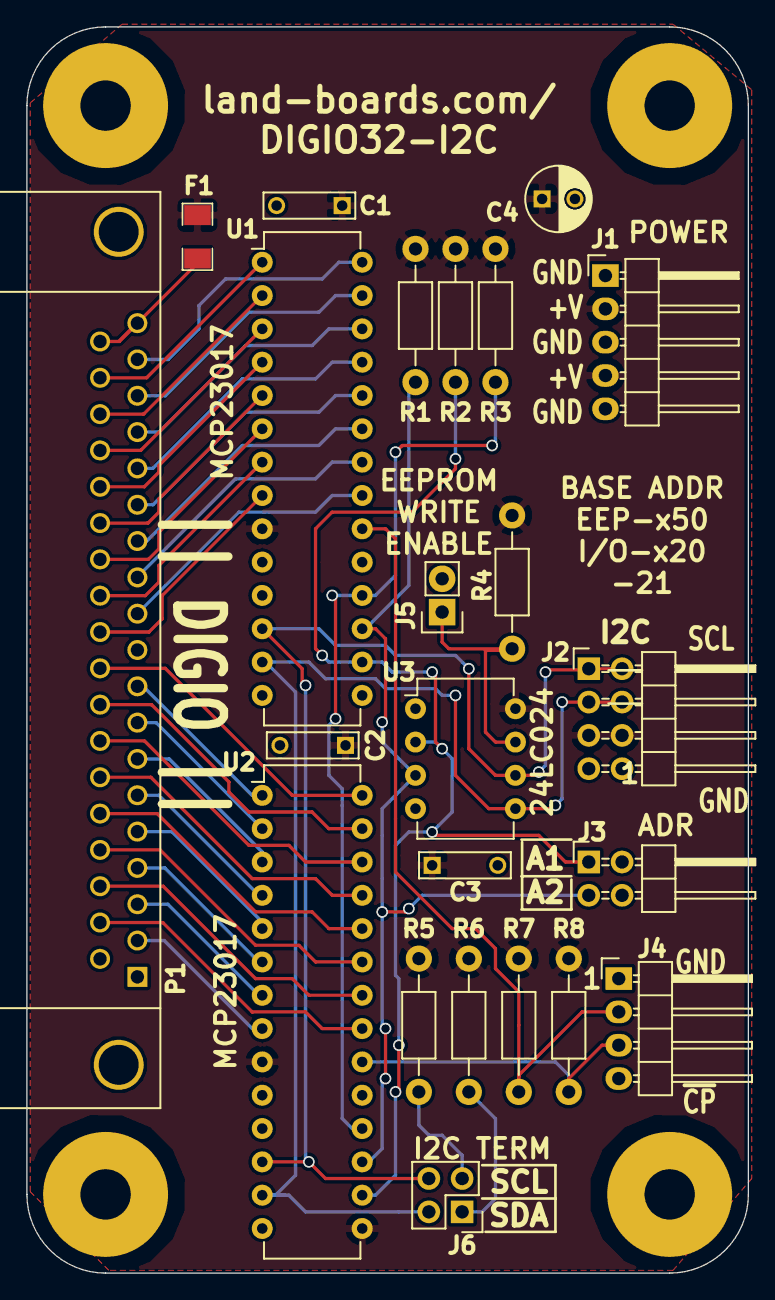
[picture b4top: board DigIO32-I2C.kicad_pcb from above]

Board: 2 copper layers, 55.0 x 95.0 mm, 28 parts (0 on the bottom side), 45 nets.

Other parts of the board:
TESTED: TESTED_COUPON; TEST_BLK-REAR
